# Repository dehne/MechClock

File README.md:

# MechClock – An Electromechanical Seven-Segment Clock Display Driven by a RaspberryPi Pico-W

# Introduction

Inspired by a [project](https://www.instructables.com/Kinetic-Digital-Clock-Arduino-3D-Print/) on the Hackaday blog that implements an seven-segment digital clock featuring 3D-printed display digits with protruding segments, each segment driven in or out by a hobby servo, I decided to make a clock with a similar display implemented very differently. Instead of servos, I chose to drive each digit's seven segments using seven cams, all ganged together on single shaft driven by a small, geared-down 28BYJ-48 stepper motor. One turn of the common cam shaft drives the display to show the digits 0 - 9 in sequence. Four identical digit display modules side by side with a fixed colon unit in the middle complete the display. Add a custom PCB with a RaspberryPi Pico-W, 3 ULN2003 Darlington pair DIP chips to drive the steppers, and an LED array/light sensor for self adjusting digit illumination, a case and some custom firmware, and whaddya know: a digital clock.

Here you'll find the firmware for the project.

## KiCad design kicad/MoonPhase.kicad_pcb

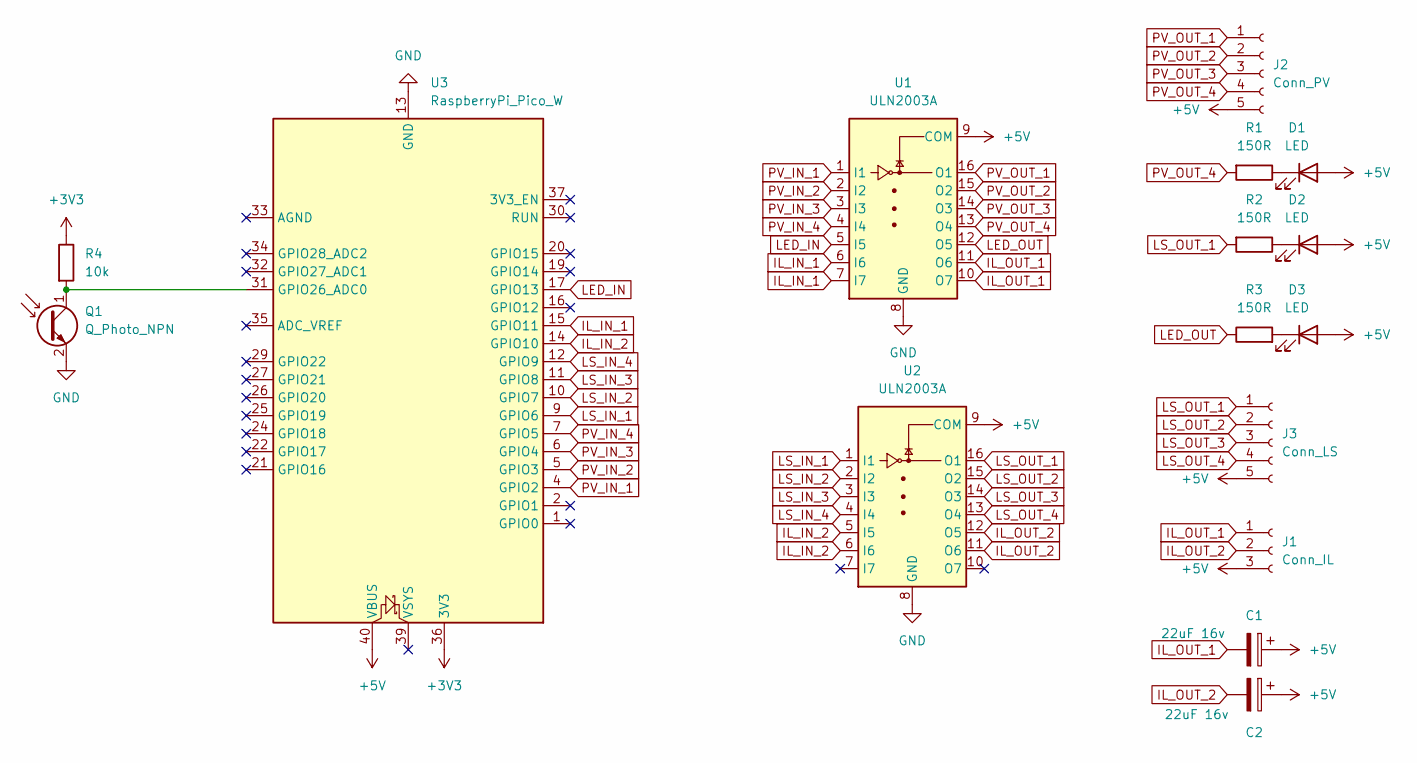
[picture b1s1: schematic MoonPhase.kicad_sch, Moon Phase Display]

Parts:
C1, C2: 22uF 16v; CP_Radial_D4.0mm_P2.00mm
D1, D2, D3: LED; LED_0805_2012Metric
J1: Conn_IL; JST_XH_B3B-XH-AM_1x03_P2.50mm_Vertical
J2: Conn_PV; JST_XH_B5B-XH-AM_1x05_P2.50mm_Vertical
J3: Conn_LS; JST_XH_B5B-XH-AM_1x05_P2.50mm_Vertical
Q1: Q_Photo_NPN; PinHeader_1x02_P2.54mm_Vertical
R1, R3: 150R; R_0805_2012Metric
R2: 150R; R_0805_2012Metric_Pad1.20x1.40mm_HandSolder
R4: 10k; R_0805_2012Metric
U1, U2: ULN2003A; CERDIP-16_W7.62mm_SideBrazed_Socket
U3: RaspberryPi_Pico_W; RaspberryPi_Pico_Common

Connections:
+3V3: R4.1, U3.36 (3V3)
+5V: C1.1, C2.1, D1.2 (A), D2.2 (A), D3.2 (A), J1.3, J2.5, J3.5, U1.9 (COM), U2.9 (COM), U3.40 (VBUS)
GND: Q1.2 (E), U1.8 (GND), U2.8 (GND), U3.3 (GND), U3.8 (GND), U3.13 (GND), U3.18 (GND), U3.23 (GND), U3.28 (GND), U3.38 (GND)
IL_IN_1: U1.6 (I6), U1.7 (I7), U3.15 (GPIO11)
IL_IN_2: U2.5 (I5), U2.6 (I6), U3.14 (GPIO10)
IL_OUT_1: C1.2, J1.1, U1.10 (O7), U1.11 (O6)
IL_OUT_2: C2.2, J1.2, U2.11 (O6), U2.12 (O5)
LED_IN: U1.5 (I5), U3.17 (GPIO13)
LED_OUT: R3.1, U1.12 (O5)
LS_IN_1: U2.1 (I1), U3.9 (GPIO6)
LS_IN_2: U2.2 (I2), U3.10 (GPIO7)
LS_IN_3: U2.3 (I3), U3.11 (GPIO8)
LS_IN_4: U2.4 (I4), U3.12 (GPIO9)
LS_OUT_1: J3.1, R2.2, U2.16 (O1)
LS_OUT_2: J3.2, U2.15 (O2)
LS_OUT_3: J3.3, U2.14 (O3)
LS_OUT_4: J3.4, U2.13 (O4)
unnamed: D1.1 (K), R1.1
unnamed: D2.1 (K), R2.1
unnamed: D3.1 (K), R3.2
unnamed: Q1.1 (C), R4.2, U3.31 (GPIO26_ADC0)
PV_IN_1: U1.1 (I1), U3.4 (GPIO2)
PV_IN_2: U1.2 (I2), U3.5 (GPIO3)
PV_IN_3: U1.3 (I3), U3.6 (GPIO4)
PV_IN_4: U1.4 (I4), U3.7 (GPIO5)
PV_OUT_1: J2.1, U1.16 (O1)
PV_OUT_2: J2.2, U1.15 (O2)
PV_OUT_3: J2.3, U1.14 (O3)
PV_OUT_4: J2.4, R1.2, U1.13 (O4)

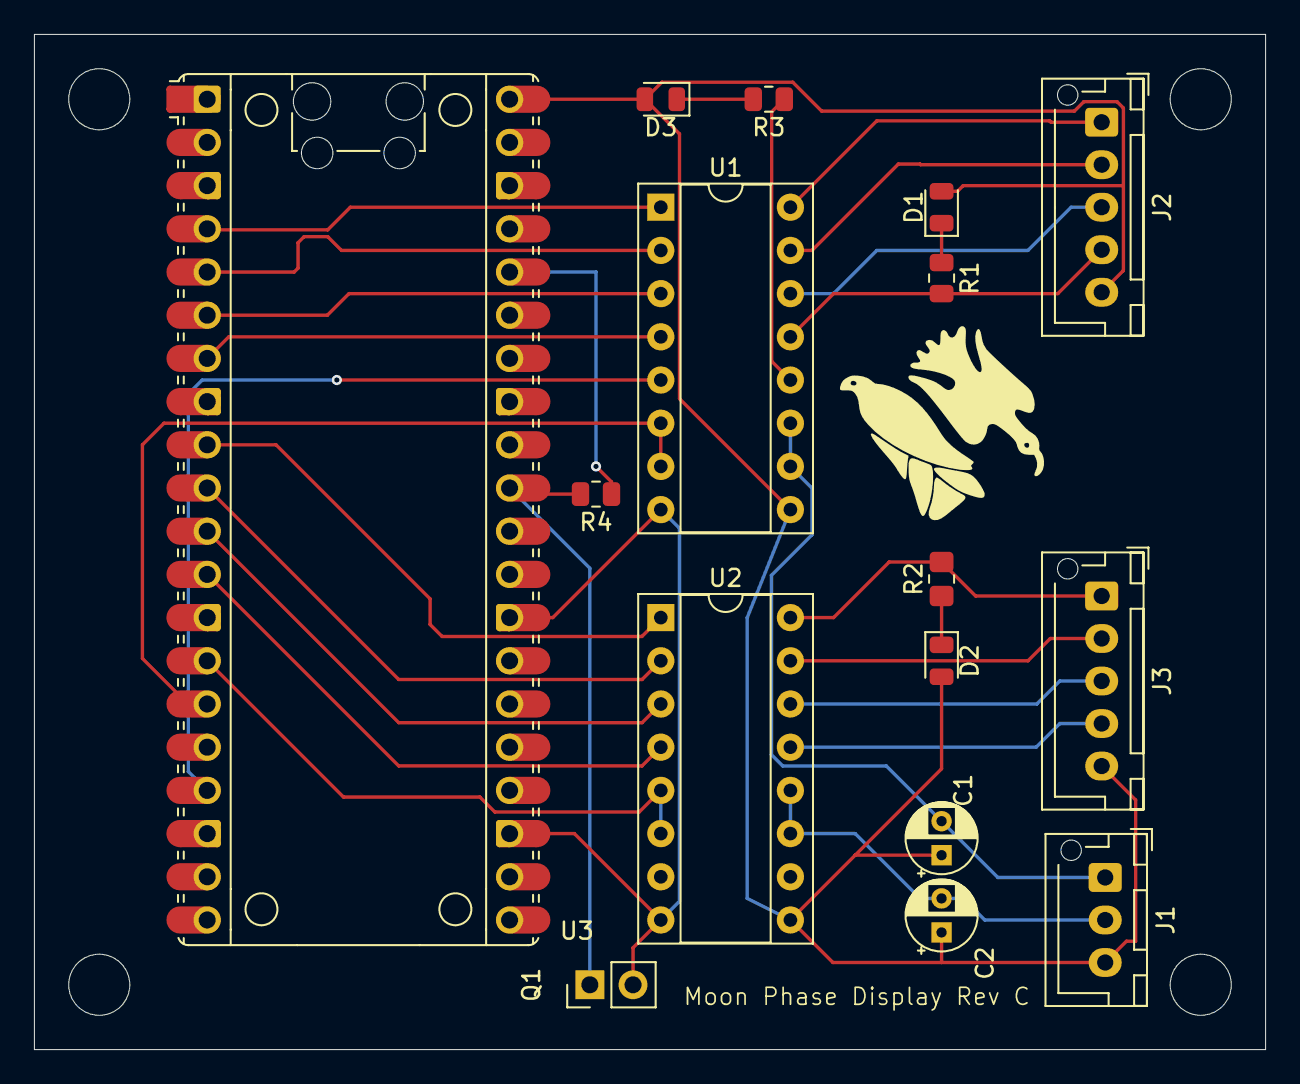
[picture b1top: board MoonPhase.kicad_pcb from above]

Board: 2 copper layers, 72.4 x 59.7 mm, 16 parts (0 on the bottom side), 29 nets.

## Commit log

2024-04-20 Change display gearing from 1:1 to 2:1
2024-05-05 Slow the rate at which the illumination changes
2024-08-20 Bring in kicad, PWM Illuminator
2024-08-20 Dispose of production files
2024-08-27 PCB Rev B
2024-09-03 Add ambient light sensor
2024-09-03 PCB Rev C Update
2025-04-16 Tweak ambient light; update documenttion
2025-04-16 Don't need my notes managed
2025-04-16 Ignore notes.md
